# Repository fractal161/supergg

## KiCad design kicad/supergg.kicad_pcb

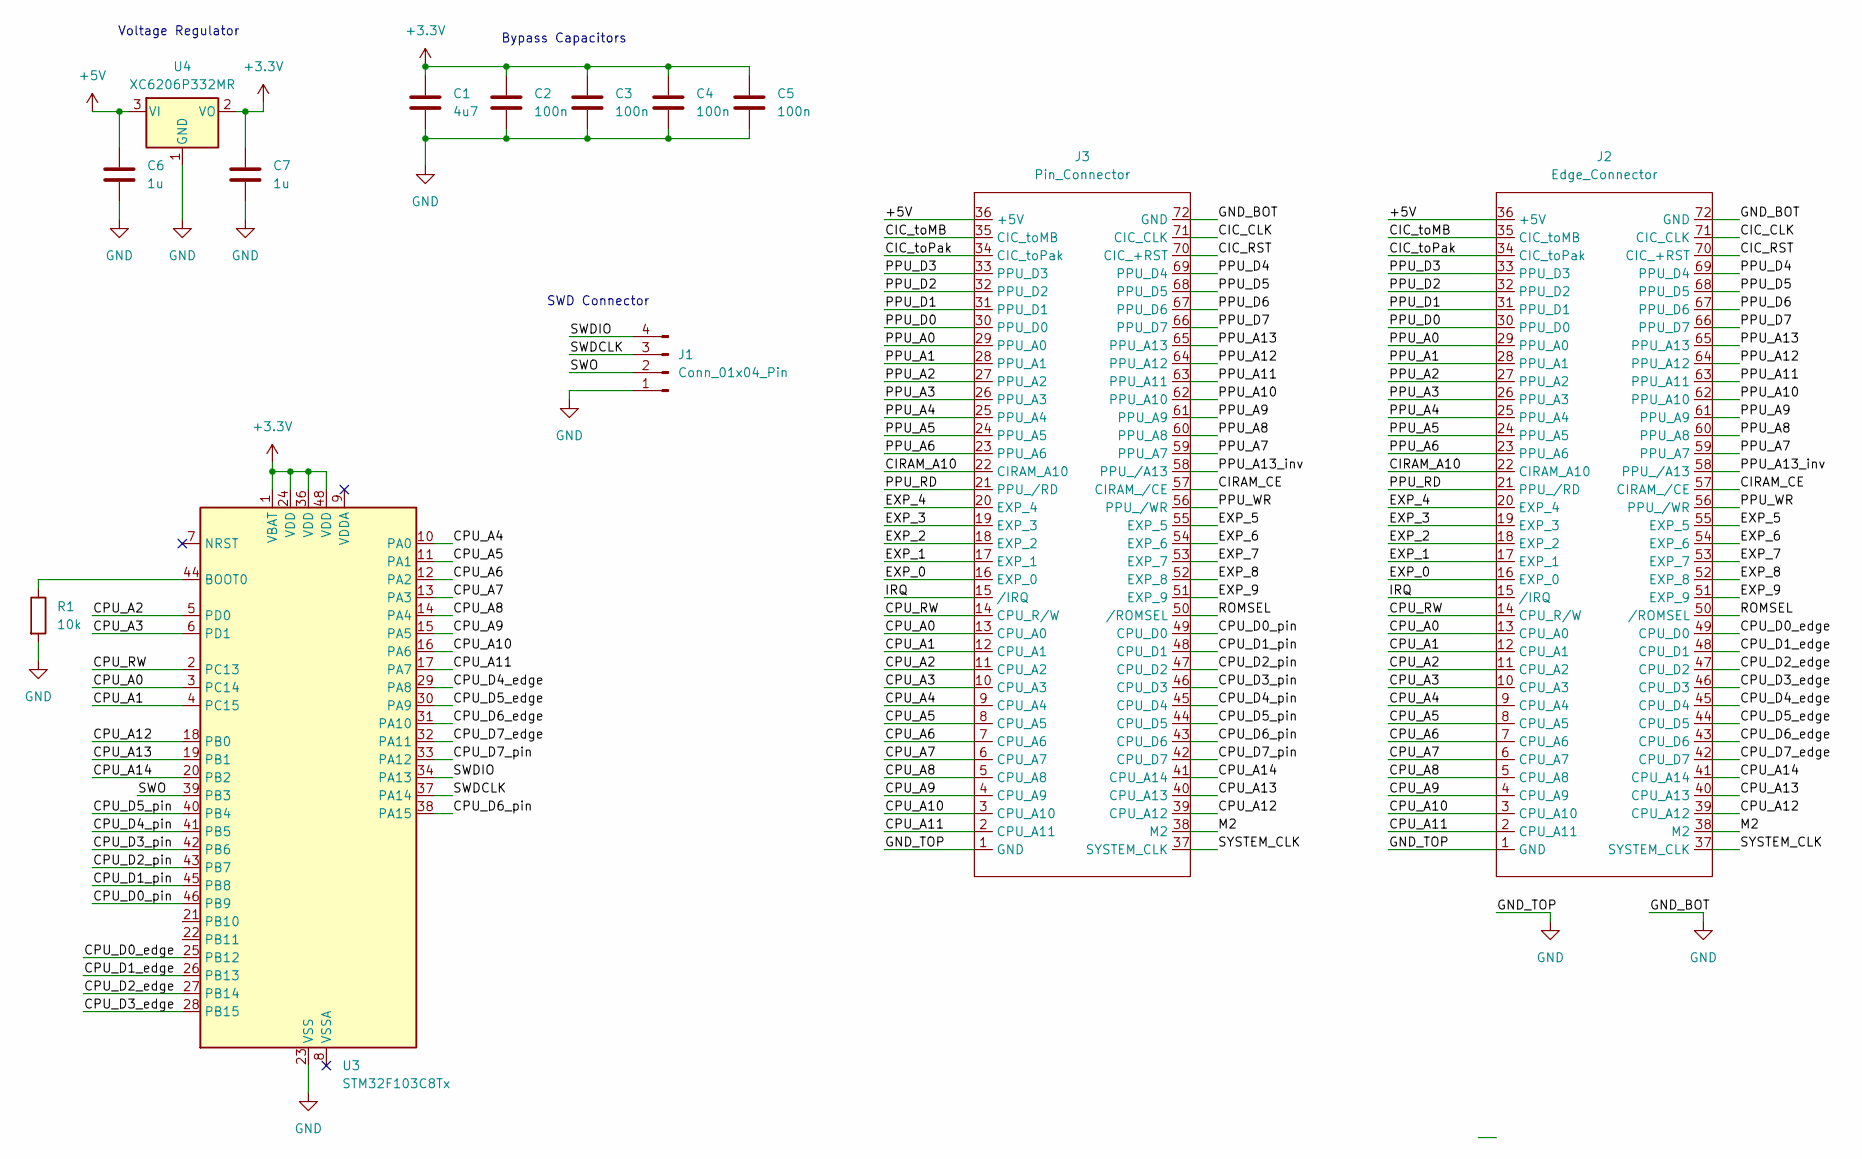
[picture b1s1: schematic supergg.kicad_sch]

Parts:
C1: 4u7; C_0603_1608Metric; LCSC C1705
C2, C3, C4, C5: 100n; C_0402_1005Metric; LCSC C1525
C6, C7: 1u; C_0603_1608Metric; LCSC C1592
J1: Conn_01x04_Pin; PinHeader_1x04_P2.54mm_Horizontal; LCSC C492412
J2: Edge_Connector
J3: Pin_Connector
R1: 10k; R_0603_1608Metric; LCSC C25804
U3: STM32F103C8Tx; LQFP-48_7x7mm_P0.5mm; LCSC C8734
U4: XC6206P332MR; SOT-23-3; LCSC C347376

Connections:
+3.3V: C1.1, C2.1, C3.1, C4.1, C5.1, C7.1, U3.1 (VBAT), U3.24 (VDD), U3.36 (VDD), U3.48 (VDD), U4.2 (VO)
+5V: C6.1, J2.36 (+5V), J3.36 (+5V), U4.3 (VI)
/CIC_CLK: J2.71 (CIC_CLK), J3.71 (CIC_CLK)
/CIC_RST: J2.70 (CIC_+RST), J3.70 (CIC_+RST)
/CIC_toMB: J2.35 (CIC_toMB), J3.35 (CIC_toMB)
/CIC_toPak: J2.34 (CIC_toPak), J3.34 (CIC_toPak)
/CIRAM_A10: J2.22 (CIRAM_A10), J3.22 (CIRAM_A10)
/CIRAM_CE: J2.57 (CIRAM_/CE), J3.57 (CIRAM_/CE)
/CPU_A0: J2.13 (CPU_A0), J3.13 (CPU_A0), U3.3 (PC14)
/CPU_A1: J2.12 (CPU_A1), J3.12 (CPU_A1), U3.4 (PC15)
/CPU_A2: J2.11 (CPU_A2), J3.11 (CPU_A2), U3.5 (PD0)
/CPU_A3: J2.10 (CPU_A3), J3.10 (CPU_A3), U3.6 (PD1)
/CPU_A4: J2.9 (CPU_A4), J3.9 (CPU_A4), U3.10 (PA0)
/CPU_A5: J2.8 (CPU_A5), J3.8 (CPU_A5), U3.11 (PA1)
/CPU_A6: J2.7 (CPU_A6), J3.7 (CPU_A6), U3.12 (PA2)
/CPU_A7: J2.6 (CPU_A7), J3.6 (CPU_A7), U3.13 (PA3)
/CPU_A8: J2.5 (CPU_A8), J3.5 (CPU_A8), U3.14 (PA4)
/CPU_A9: J2.4 (CPU_A9), J3.4 (CPU_A9), U3.15 (PA5)
/CPU_A10: J2.3 (CPU_A10), J3.3 (CPU_A10), U3.16 (PA6)
/CPU_A11: J2.2 (CPU_A11), J3.2 (CPU_A11), U3.17 (PA7)
/CPU_A12: J2.39 (CPU_A12), J3.39 (CPU_A12), U3.18 (PB0)
/CPU_A13: J2.40 (CPU_A13), J3.40 (CPU_A13), U3.19 (PB1)
/CPU_A14: J2.41 (CPU_A14), J3.41 (CPU_A14), U3.20 (PB2)
/CPU_D0_edge: J2.49 (CPU_D0), U3.25 (PB12)
/CPU_D0_pin: J3.49 (CPU_D0), U3.46 (PB9)
/CPU_D1_edge: J2.48 (CPU_D1), U3.26 (PB13)
/CPU_D1_pin: J3.48 (CPU_D1), U3.45 (PB8)
/CPU_D2_edge: J2.47 (CPU_D2), U3.27 (PB14)
/CPU_D2_pin: J3.47 (CPU_D2), U3.43 (PB7)
/CPU_D3_edge: J2.46 (CPU_D3), U3.28 (PB15)
/CPU_D3_pin: J3.46 (CPU_D3), U3.42 (PB6)
/CPU_D4_edge: J2.45 (CPU_D4), U3.29 (PA8)
/CPU_D4_pin: J3.45 (CPU_D4), U3.41 (PB5)
/CPU_D5_edge: J2.44 (CPU_D5), U3.30 (PA9)
/CPU_D5_pin: J3.44 (CPU_D5), U3.40 (PB4)
/CPU_D6_edge: J2.43 (CPU_D6), U3.31 (PA10)
/CPU_D6_pin: J3.43 (CPU_D6), U3.38 (PA15)
/CPU_D7_edge: J2.42 (CPU_D7), U3.32 (PA11)
/CPU_D7_pin: J3.42 (CPU_D7), U3.33 (PA12)
/CPU_RW: J2.14 (CPU_R/W), J3.14 (CPU_R/W), U3.2 (PC13)
/EXP_0: J2.16 (EXP_0), J3.16 (EXP_0)
/EXP_1: J2.17 (EXP_1), J3.17 (EXP_1)
/EXP_2: J2.18 (EXP_2), J3.18 (EXP_2)
/EXP_3: J2.19 (EXP_3), J3.19 (EXP_3)
/EXP_4: J2.20 (EXP_4), J3.20 (EXP_4)
/EXP_5: J2.55 (EXP_5), J3.55 (EXP_5)
/EXP_6: J2.54 (EXP_6), J3.54 (EXP_6)
/EXP_7: J2.53 (EXP_7), J3.53 (EXP_7)
/EXP_8: J2.52 (EXP_8), J3.52 (EXP_8)
/EXP_9: J2.51 (EXP_9), J3.51 (EXP_9)
/IRQ: J2.15 (/IRQ), J3.15 (/IRQ)
/M2: J2.38 (M2), J3.38 (M2)
/PPU_A0: J2.29 (PPU_A0), J3.29 (PPU_A0)
/PPU_A1: J2.28 (PPU_A1), J3.28 (PPU_A1)
/PPU_A2: J2.27 (PPU_A2), J3.27 (PPU_A2)
/PPU_A3: J2.26 (PPU_A3), J3.26 (PPU_A3)
/PPU_A4: J2.25 (PPU_A4), J3.25 (PPU_A4)
/PPU_A5: J2.24 (PPU_A5), J3.24 (PPU_A5)
/PPU_A6: J2.23 (PPU_A6), J3.23 (PPU_A6)
/PPU_A7: J2.59 (PPU_A7), J3.59 (PPU_A7)
/PPU_A8: J2.60 (PPU_A8), J3.60 (PPU_A8)
/PPU_A9: J2.61 (PPU_A9), J3.61 (PPU_A9)
/PPU_A10: J2.62 (PPU_A10), J3.62 (PPU_A10)
/PPU_A11: J2.63 (PPU_A11), J3.63 (PPU_A11)
/PPU_A12: J2.64 (PPU_A12), J3.64 (PPU_A12)
/PPU_A13: J2.65 (PPU_A13), J3.65 (PPU_A13)
/PPU_A13_inv: J2.58 (PPU_/A13), J3.58 (PPU_/A13)
/PPU_D0: J2.30 (PPU_D0), J3.30 (PPU_D0)
/PPU_D1: J2.31 (PPU_D1), J3.31 (PPU_D1)
/PPU_D2: J2.32 (PPU_D2), J3.32 (PPU_D2)
/PPU_D3: J2.33 (PPU_D3), J3.33 (PPU_D3)
/PPU_D4: J2.69 (PPU_D4), J3.69 (PPU_D4)
/PPU_D5: J2.68 (PPU_D5), J3.68 (PPU_D5)
/PPU_D6: J2.67 (PPU_D6), J3.67 (PPU_D6)
/PPU_D7: J2.66 (PPU_D7), J3.66 (PPU_D7)
/PPU_RD: J2.21 (PPU_/RD), J3.21 (PPU_/RD)
/PPU_WR: J2.56 (PPU_/WR), J3.56 (PPU_/WR)
/ROMSEL: J2.50 (/ROMSEL), J3.50 (/ROMSEL)
/SWDCLK: J1.3, U3.37 (PA14)
/SWDIO: J1.4, U3.34 (PA13)
/SWO: J1.2, U3.39 (PB3)
/SYSTEM_CLK: J2.37 (SYSTEM_CLK), J3.37 (SYSTEM_CLK)
GND: C1.2, C2.2, C3.2, C4.2, C5.2, C6.2, C7.2, J1.1, J2.1 (GND), J2.72 (GND), J3.1 (GND), J3.72 (GND), R1.2, U3.23 (VSS), U3.35 (VSS), U3.47 (VSS), U4.1 (GND)
unnamed: R1.1, U3.44 (BOOT0)

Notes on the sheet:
Bypass Capacitors
Voltage Regulator
SWD Connector

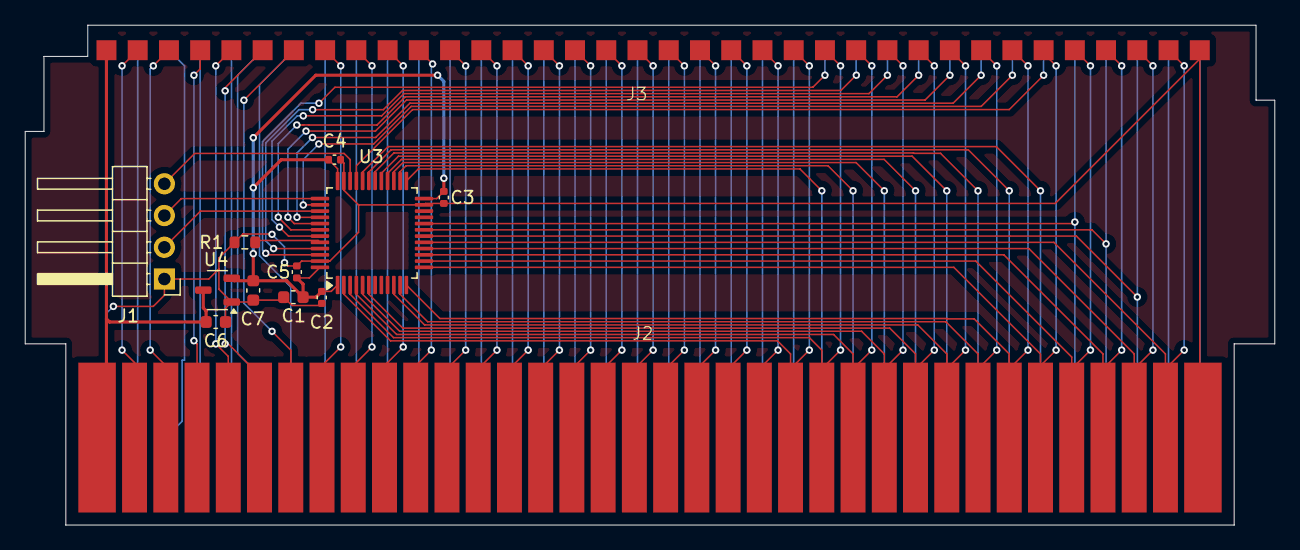
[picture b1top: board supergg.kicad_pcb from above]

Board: 4 copper layers, 100.0 x 40.0 mm, 13 parts (0 on the bottom side), 84 nets.

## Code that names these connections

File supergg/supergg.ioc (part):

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Mcu.Name=STM32F103C(8-B)Tx
Mcu.Package=LQFP48
Mcu.UserName=STM32F103C8Tx
PA12.Signal=GPXTI12
PA13.Signal=GPIO_Input
PA14.Signal=GPIO_Input
PA15.Signal=GPIO_Input
PA5.GPIOParameters=GPIO_PuPd,GPIO_ModeDefaultOutputPP
PA5.GPIO_ModeDefaultOutputPP=GPIO_MODE_OUTPUT_OD
PA5.GPIO_PuPd=GPIO_NOPULL
PA5.Signal=GPIO_Output
PA6.GPIOParameters=GPIO_PuPd,GPIO_ModeDefaultOutputPP
PA6.GPIO_ModeDefaultOutputPP=GPIO_MODE_OUTPUT_OD
PA6.GPIO_PuPd=GPIO_NOPULL
PA6.Signal=GPIO_Output
PA7.GPIOParameters=GPIO_PuPd,GPIO_ModeDefaultOutputPP
PA7.GPIO_ModeDefaultOutputPP=GPIO_MODE_OUTPUT_OD
PA7.GPIO_PuPd=GPIO_NOPULL
PA7.Signal=GPIO_Output
PB0.GPIOParameters=GPIO_PuPd,GPIO_ModeDefaultOutputPP
PB0.GPIO_ModeDefaultOutputPP=GPIO_MODE_OUTPUT_OD
PB0.GPIO_PuPd=GPIO_NOPULL
PB0.Signal=GPIO_Output
PB1.GPIOParameters=GPIO_PuPd,GPIO_ModeDefaultOutputPP
PB1.GPIO_ModeDefaultOutputPP=GPIO_MODE_OUTPUT_OD
PB1.GPIO_PuPd=GPIO_NOPULL
PB1.Signal=GPIO_Output
PB10.GPIOParameters=GPIO_PuPd,GPIO_ModeDefaultOutputPP
PB10.GPIO_ModeDefaultOutputPP=GPIO_MODE_OUTPUT_OD
PB10.GPIO_PuPd=GPIO_NOPULL
PB10.Signal=GPIO_Output
PB11.GPIOParameters=GPIO_PuPd,GPIO_ModeDefaultOutputPP
PB11.GPIO_ModeDefaultOutputPP=GPIO_MODE_OUTPUT_OD
PB11.GPIO_PuPd=GPIO_NOPULL
PB11.Signal=GPIO_Output
PB2.GPIOParameters=GPIO_PuPd,GPIO_ModeDefaultOutputPP
PB2.GPIO_ModeDefaultOutputPP=GPIO_MODE_OUTPUT_OD
PB2.GPIO_PuPd=GPIO_NOPULL
PB2.Signal=GPIO_Output
PB3.Signal=GPIO_Input
PB4.Signal=GPIO_Input
PB5.Signal=GPIO_Input
PB6.Signal=GPIO_Input
PB7.Signal=GPIO_Input
PB8.Signal=GPIO_Input
RCC.SYSCLKFreq_VALUE=64000000
RCC.SYSCLKSource=RCC_SYSCLKSOURCE_PLLCLK
board=custom

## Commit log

2025-07-06 nes cart pcb cutout
2025-07-06 add pin connector holes
2025-07-06 add edge connector symbol
2025-07-07 add edge connector footprint
2025-07-08 empty stm32cubeide project
2025-07-08 add symbols and footprints for most parts
2025-07-08 refactor connectors
2025-07-08 add wiring
2025-07-09 rework wiring
2025-07-09 finish first draft of wiring
